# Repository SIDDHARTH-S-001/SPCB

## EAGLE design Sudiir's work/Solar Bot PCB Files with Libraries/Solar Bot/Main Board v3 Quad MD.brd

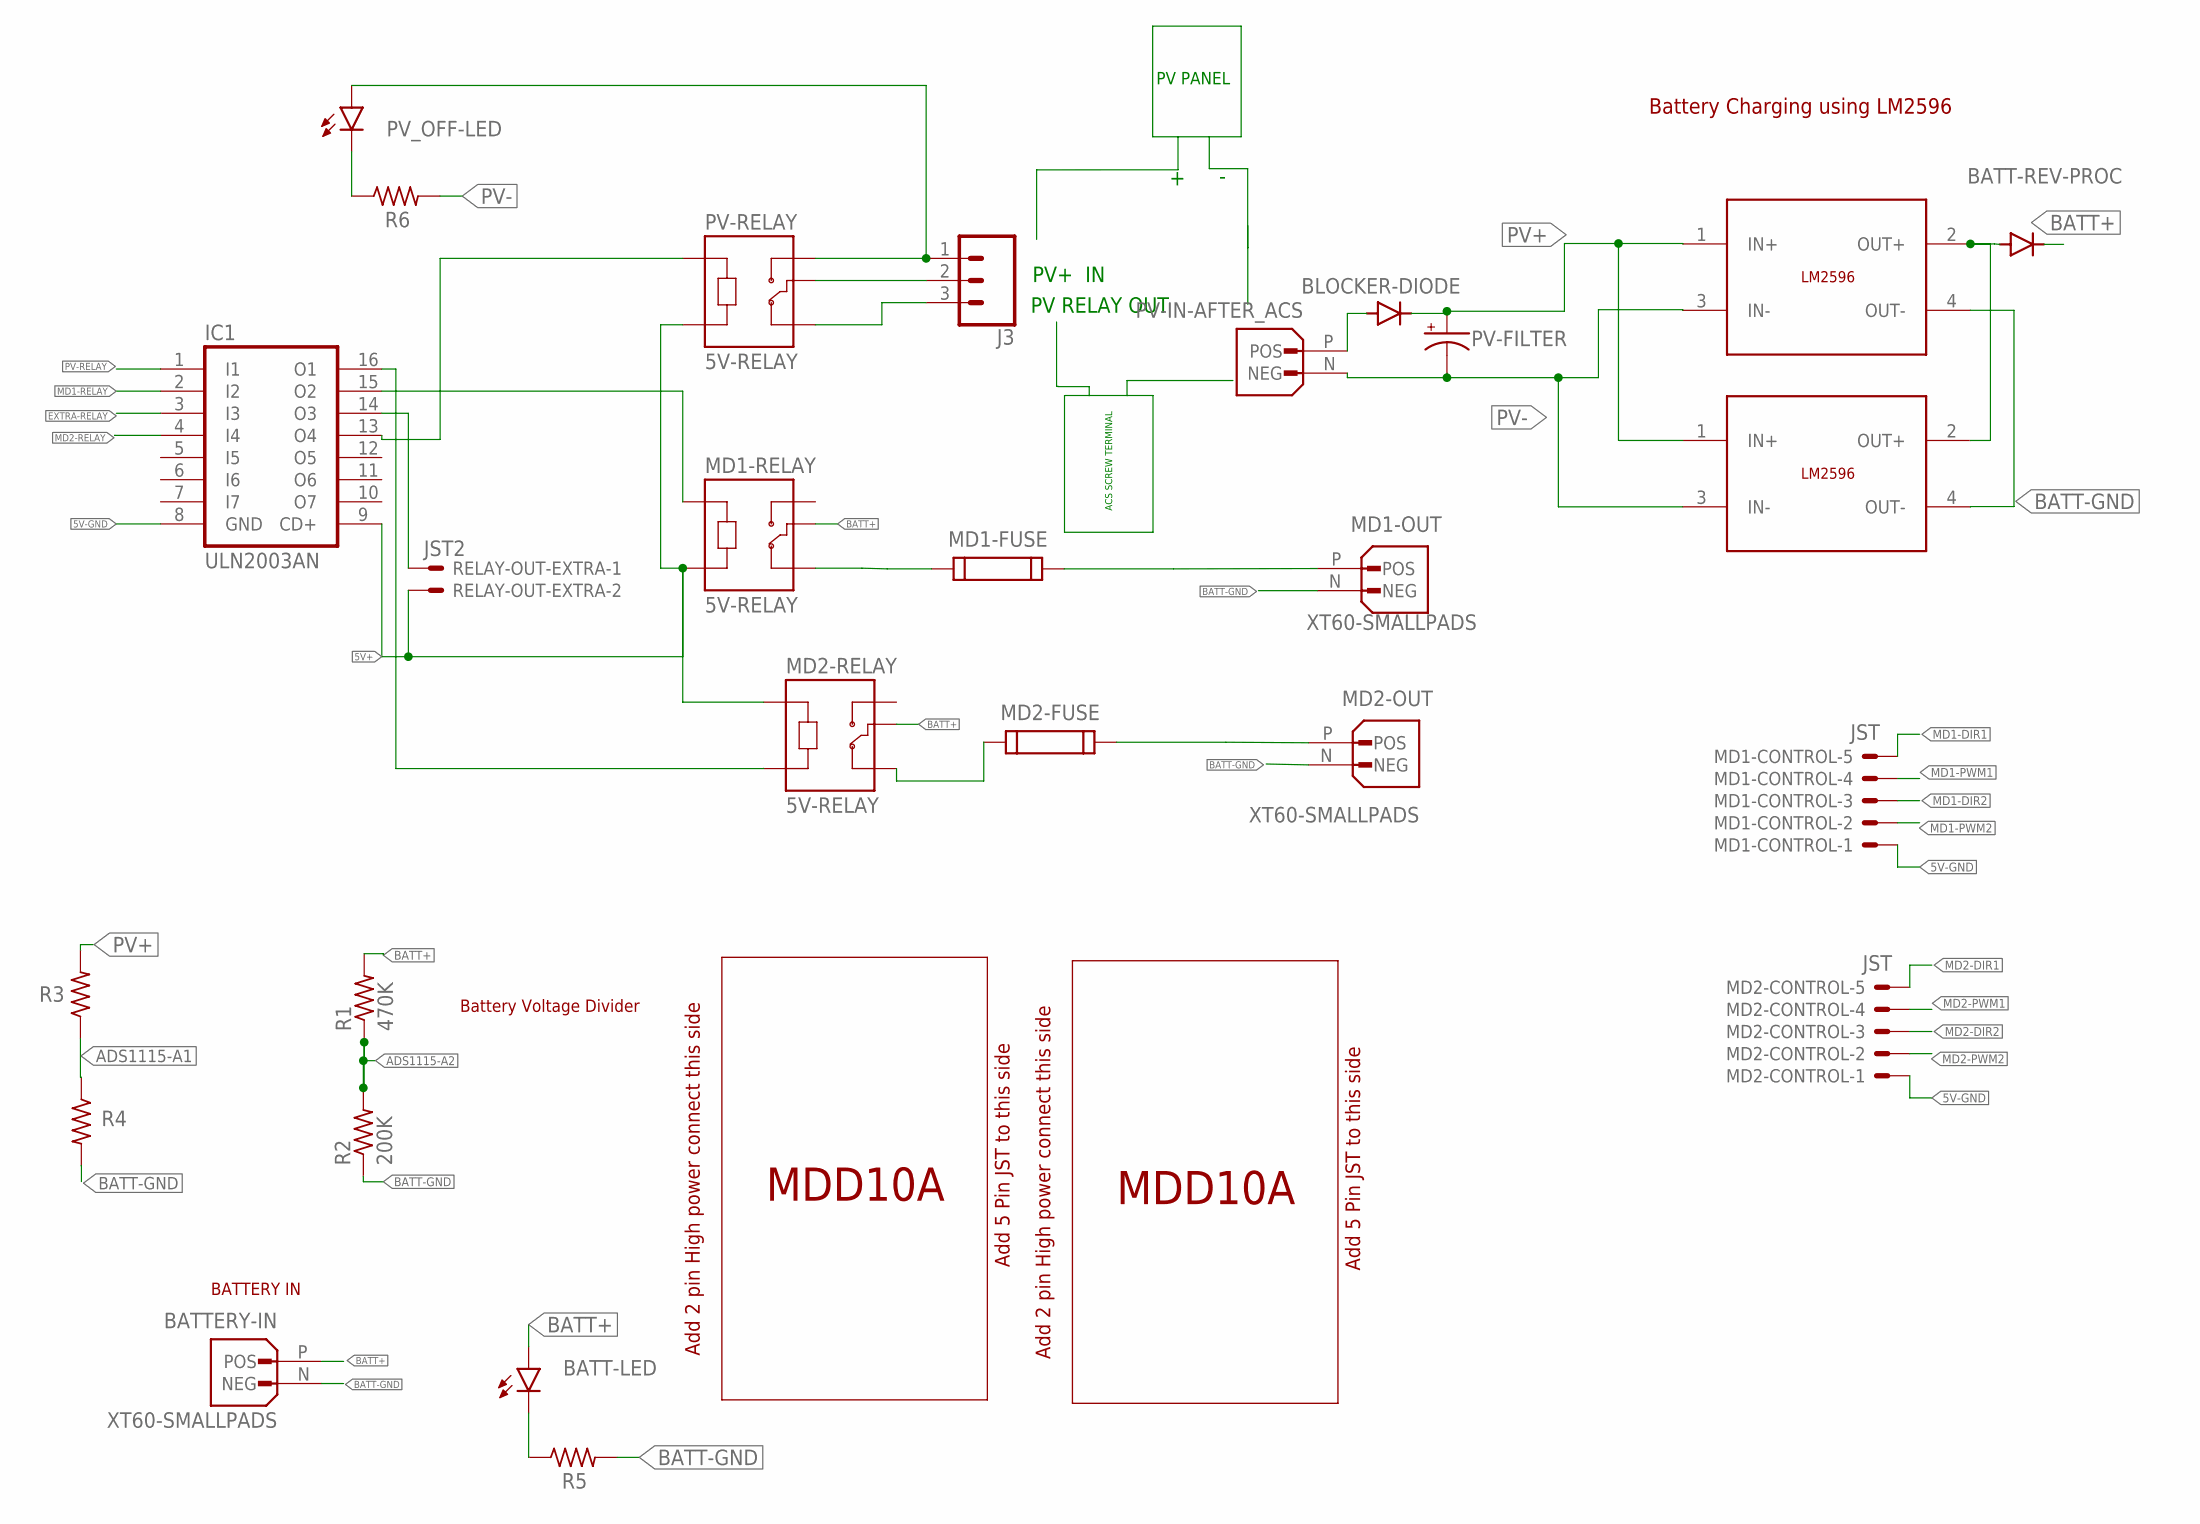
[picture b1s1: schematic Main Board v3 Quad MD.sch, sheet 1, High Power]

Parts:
BATT-LED: SFH482
BATT-REV-PROC: 1N5400; DO201-15
BATTERY-IN: XT60-SMALLPADS; XT-60-SMALLPADS
BLOCKER-DIODE: 1N5400; DO201-15
IC1: ULN2003AN; DIL16
J3: CONN_03SCREW_LOCK; SCREWTERMINAL-3.5MM-3_LOCK.007S
MD1-CONTROL, MD2-CONTROL: JST; JST-XH-05-PACKAGE-LONG-PAD
MD1-FUSE, MD2-FUSE: 696101000002
MD1-OUT, MD2-OUT: XT60-SMALLPADS; XT-60-SMALLPADS
MD1-RELAY, MD2-RELAY: 5V-RELAY; RELAY-SRD-05VDC-SL-C
PV-FILTER: CPOL-USE5-6; E5-6
PV-IN-AFTER_ACS: XT60-SMALLPADS; XT-60-SMALLPADS
PV-RELAY: 5V-RELAY; RELAY-SRD-05VDC-SL-C
PV_OFF-LED: SFH482
R1: 470K; 0309/12
R2: 200K; 0309/12
R3, R4, R5, R6: R-US_0309/12; 0309/12
RELAY-OUT-EXTRA: JST2; JST-XH-02-PACKAGE-LONG-PAD
U$1, U$2: LM2596-MODULE
U$3, U$7: MDD10A-MODULE; MDD10A

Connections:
5V+: IC1.9 (CD+), MD1-RELAY.A2, MD2-RELAY.A1, PV-RELAY.A2, RELAY-OUT-EXTRA.2; also elsewhere on the board
5V-GND: IC1.8 (GND), MD1-CONTROL.1, MD2-CONTROL.1; also elsewhere on the board
ADS1115-A1: R3.1, R4.1; also elsewhere on the board
ADS1115-A2: R1.1, R2.2; also elsewhere on the board
BATT+: BATT-LED.A, BATT-REV-PROC.C, BATTERY-IN.P (POS), MD1-RELAY.COM, MD2-RELAY.COM, R1.2; also elsewhere on the board
BATT-GND: BATTERY-IN.N (NEG), MD1-OUT.N (NEG), MD2-OUT.N (NEG), R2.1, R4.2, R5.2, U$1.4 (OUT-), U$2.4 (OUT-); also elsewhere on the board
EXTRA-RELAY: IC1.3 (I3); also elsewhere on the board
MD1-DIR1: MD1-CONTROL.5; also elsewhere on the board
MD1-DIR2: MD1-CONTROL.3; also elsewhere on the board
MD1-PWM1: MD1-CONTROL.4; also elsewhere on the board
MD1-PWM2: MD1-CONTROL.2; also elsewhere on the board
MD1-RELAY: IC1.2 (I2); also elsewhere on the board
MD2-DIR1: MD2-CONTROL.5; also elsewhere on the board
MD2-DIR2: MD2-CONTROL.3; also elsewhere on the board
MD2-PWM1: MD2-CONTROL.4; also elsewhere on the board
MD2-PWM2: MD2-CONTROL.2; also elsewhere on the board
MD2-RELAY: IC1.4 (I4); also elsewhere on the board
unnamed: MD1-FUSE.2, MD1-OUT.P (POS)
unnamed: IC1.14 (O3), RELAY-OUT-EXTRA.1
unnamed: J3.1, PV-RELAY.NO, PV_OFF-LED.A
unnamed: J3.2, PV-RELAY.COM
unnamed: MD1-FUSE.1, MD1-RELAY.NC
unnamed: MD2-FUSE.1, MD2-RELAY.NC
unnamed: BLOCKER-DIODE.A, PV-IN-AFTER_ACS.P (POS)
unnamed: IC1.16 (O1), MD2-RELAY.A2
unnamed: MD2-FUSE.2, MD2-OUT.P (POS)
unnamed: BATT-REV-PROC.A, U$1.2 (OUT+), U$2.2 (OUT+)
unnamed: IC1.13 (O4), PV-RELAY.A1
unnamed: BATT-LED.K (C), R5.1
unnamed: PV_OFF-LED.K (C), R6.1
unnamed: J3.3, PV-RELAY.NC
unnamed: IC1.15 (O2), MD1-RELAY.A1
PV+: BLOCKER-DIODE.C, PV-FILTER.+, R3.2, U$1.1 (IN+), U$2.1 (IN+)
PV-: PV-FILTER.-, PV-IN-AFTER_ACS.N (NEG), R6.2, U$1.3 (IN-), U$2.3 (IN-)
PV-RELAY: IC1.1 (I1); also elsewhere on the board

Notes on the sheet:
PV+ IN
PV RELAY OUT
ACS SCREW TERMINAL
PV PANEL
Battery Voltage Divider
BATTERY IN
Battery Charging using LM2596

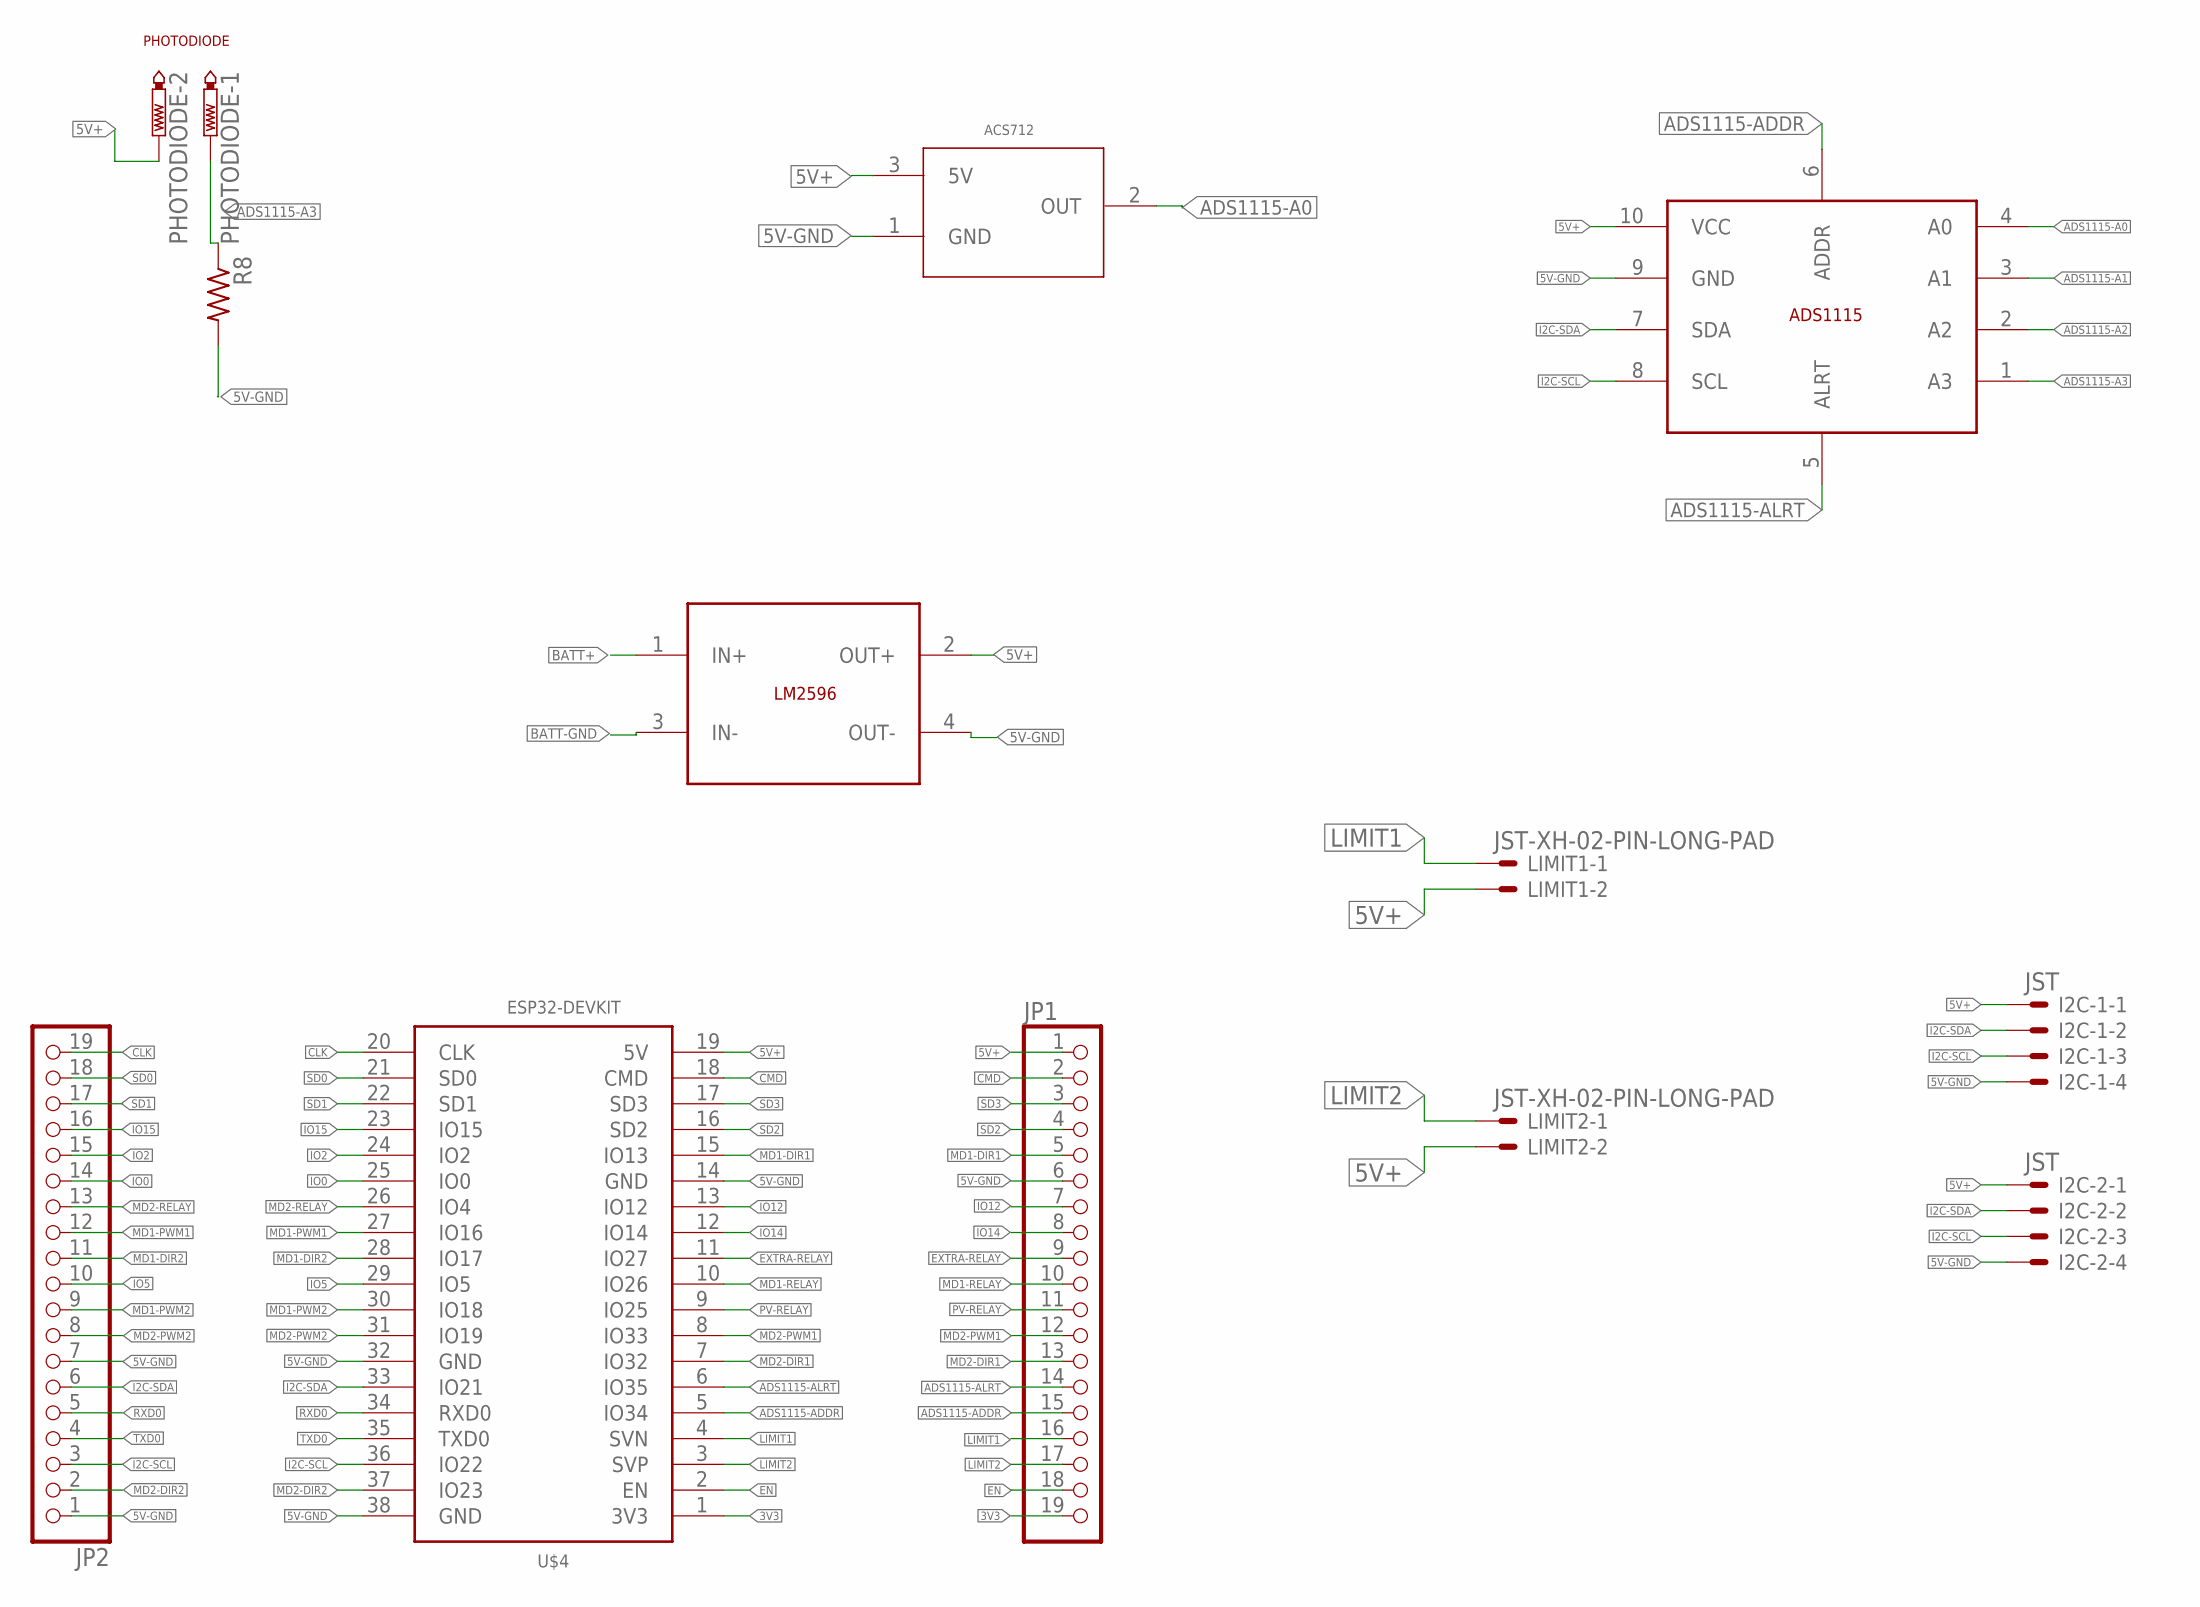
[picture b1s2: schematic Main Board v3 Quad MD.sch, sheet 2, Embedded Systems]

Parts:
I2C-1, I2C-2: JST; JST-XH-04-PACKAGE-LONG-PAD
JP1, JP2: PINHD-1X19; 1X19
LIMIT1, LIMIT2: JST-XH-02-PIN-LONG-PAD; JST-XH-02-PACKAGE-LONG-PAD
PHOTODIODE: PTR2; P2-38-17
R8: R-US_0309/12; 0309/12
U$4: ESP32-DEVKIT; ESP32-38PINS
U$5: ACS712-MODULE
U$6: ADS1115-MODULE
U$8: LM2596-MODULE

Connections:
3V3: JP1.19, U$4.1 (3V3)
5V+: I2C-1.1, I2C-2.1, JP1.1, LIMIT1.2, LIMIT2.2, PHOTODIODE.TP-2, U$4.19 (5V), U$5.3 (5V), U$6.10 (VCC), U$8.2 (OUT+); also elsewhere on the board
5V-GND: I2C-1.4, I2C-2.4, JP1.6, JP2.1, JP2.7, R8.2, U$4.14 (GND), U$4.32 (GND), U$4.38 (GND), U$5.1 (GND), U$6.9 (GND), U$8.4 (OUT-); also elsewhere on the board
ADS1115-A0: U$5.2 (OUT), U$6.4 (A0)
ADS1115-A1: U$6.3 (A1); also elsewhere on the board
ADS1115-A2: U$6.2 (A2); also elsewhere on the board
ADS1115-A3: PHOTODIODE.TP-1, R8.1, U$6.1 (A3)
ADS1115-ADDR: JP1.15, U$4.5 (IO34), U$6.6 (ADDR)
ADS1115-ALRT: JP1.14, U$4.6 (IO35), U$6.5 (ALRT)
BATT+: U$8.1 (IN+); also elsewhere on the board
BATT-GND: U$8.3 (IN-); also elsewhere on the board
CLK: JP2.19, U$4.20 (CLK)
CMD: JP1.2, U$4.18 (CMD)
EN: JP1.18, U$4.2 (EN)
EXTRA-RELAY: JP1.9, U$4.11 (IO27); also elsewhere on the board
I2C-SCL: I2C-1.3, I2C-2.3, JP2.3, U$4.36 (IO22), U$6.8 (SCL)
I2C-SDA: I2C-1.2, I2C-2.2, JP2.6, U$4.33 (IO21), U$6.7 (SDA)
IO0: JP2.14, U$4.25 (IO0)
IO2: JP2.15, U$4.24 (IO2)
IO5: JP2.10, U$4.29 (IO5)
IO12: JP1.7, U$4.13 (IO12)
IO14: JP1.8, U$4.12 (IO14)
IO15: JP2.16, U$4.23 (IO15)
LIMIT1: JP1.16, LIMIT1.1, U$4.4 (SVN)
LIMIT2: JP1.17, LIMIT2.1, U$4.3 (SVP)
MD1-DIR1: JP1.5, U$4.15 (IO13); also elsewhere on the board
MD1-DIR2: JP2.11, U$4.28 (IO17); also elsewhere on the board
MD1-PWM1: JP2.12, U$4.27 (IO16); also elsewhere on the board
MD1-PWM2: JP2.9, U$4.30 (IO18); also elsewhere on the board
MD1-RELAY: JP1.10, U$4.10 (IO26); also elsewhere on the board
MD2-DIR1: JP1.13, U$4.7 (IO32); also elsewhere on the board
MD2-DIR2: JP2.2, U$4.37 (IO23); also elsewhere on the board
MD2-PWM1: JP1.12, U$4.8 (IO33); also elsewhere on the board
MD2-PWM2: JP2.8, U$4.31 (IO19); also elsewhere on the board
MD2-RELAY: JP2.13, U$4.26 (IO4); also elsewhere on the board
PV-RELAY: JP1.11, U$4.9 (IO25); also elsewhere on the board
RXD0: JP2.5, U$4.34 (RXD0)
SD0: JP2.18, U$4.21 (SD0)
SD1: JP2.17, U$4.22 (SD1)
SD2: JP1.4, U$4.16 (SD2)
SD3: JP1.3, U$4.17 (SD3)
TXD0: JP2.4, U$4.35 (TXD0)

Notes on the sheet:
PHOTODIODE

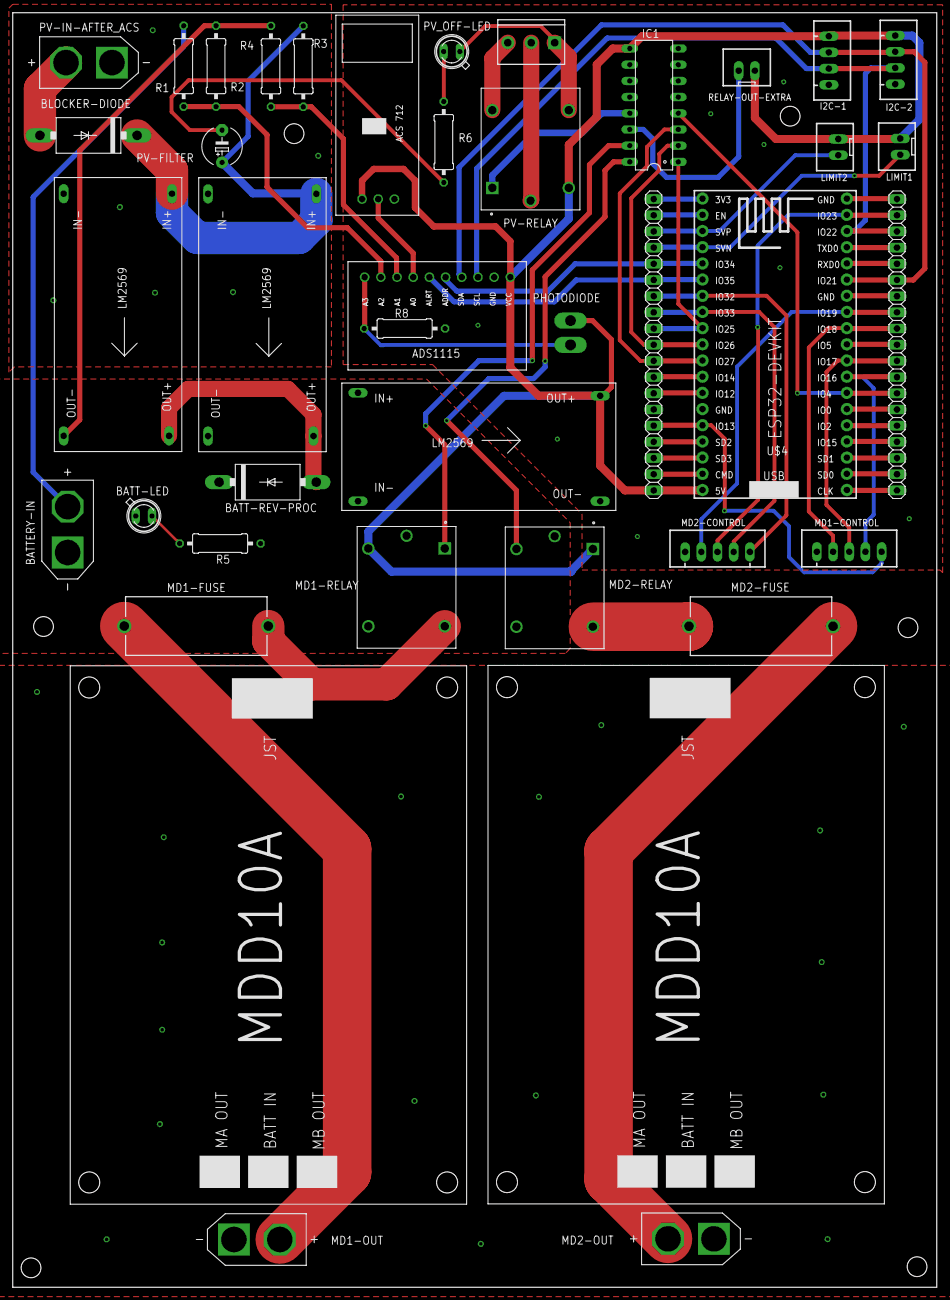
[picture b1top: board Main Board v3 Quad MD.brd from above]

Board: 2 copper layers, 145.0 x 200.0 mm, 41 parts (0 on the bottom side), 59 nets.

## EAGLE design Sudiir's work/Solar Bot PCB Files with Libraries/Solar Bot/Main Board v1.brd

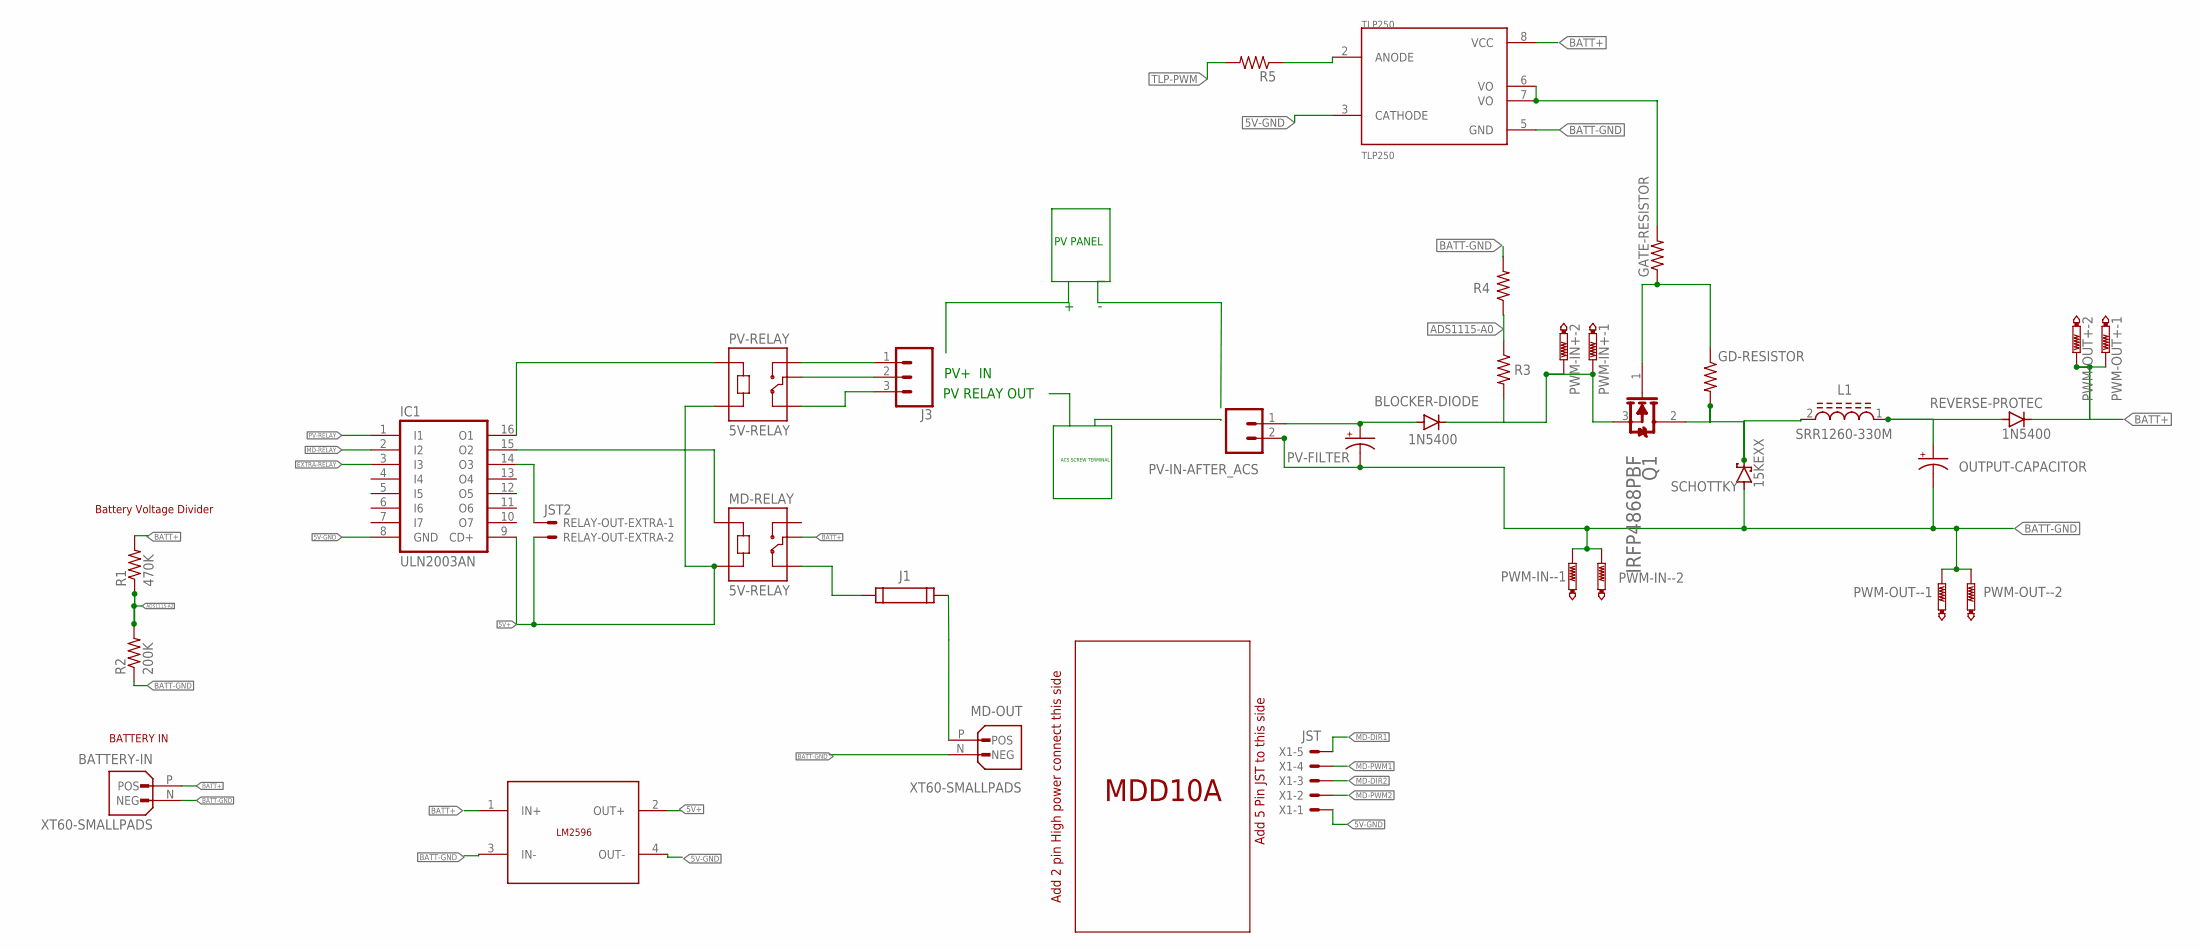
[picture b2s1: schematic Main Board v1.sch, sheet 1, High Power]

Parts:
BATTERY-IN: XT60-SMALLPADS; XT-60-SMALLPADS
BLOCKER-DIODE: 1N5400; DO201-15
GATE-RESISTOR: R-US_0309/12; 0309/12
GD-RESISTOR: R-US_0309/12; 0309/12
IC1: ULN2003AN; DIL16
J1: 696101000002
J3: CONN_03SCREW_LOCK; SCREWTERMINAL-3.5MM-3_LOCK.007S
L1: SRR1260-330M; INDP125125X600N
MD-OUT: XT60-SMALLPADS; XT-60-SMALLPADS
MD-RELAY: 5V-RELAY; RELAY-SRD-05VDC-SL-C
OUTPUT-CAPACITOR: 1000UF-RADIAL-5MM-25V-20%-NO-SILK; CPOL-RADIAL-5MM-10MM-NS
PV-FILTER: 1000UF-RADIAL-5MM-25V-20%-NO-SILK; CPOL-RADIAL-5MM-10MM-NS
PV-IN-AFTER_ACS: CONN_023.5MM; SCREWTERMINAL-3.5MM-2
PV-RELAY: 5V-RELAY; RELAY-SRD-05VDC-SL-C
PWM-IN+: PTR2; P2-38-17
PWM-IN-: PTR2; P2-38-17
PWM-OUT+: PTR2; P2-38-17
PWM-OUT-: PTR2; P2-38-17
Q1: INFINEON_IRFP4868PBFINFINEON_IRFP4868PBF_0_0; INFINEON_IRFP4868PBF_0
R1: 470K; 0309/12
R2: 200K; 0309/12
R3, R4, R5: R-US_0309/12; 0309/12
RELAY-OUT-EXTRA: JST2; JST-XH-02-PACKAGE-LONG-PAD
REVERSE-PROTEC: 1N5400; DO201-15
SCHOTTKY: 15KEXX; CB429-17
TLP250: TLP250; DIP8
U$2: MDD10A-MODULE; MDD10A
U$5: LM2596-MODULE
X1: JST; JST-XH-05-PACKAGE-LONG-PAD

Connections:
5V+: IC1.9 (CD+), MD-RELAY.A2, PV-RELAY.A2, RELAY-OUT-EXTRA.2, U$5.2 (OUT+); also elsewhere on the board
5V-GND: IC1.8 (GND), TLP250.3 (CATHODE), U$5.4 (OUT-), X1.1; also elsewhere on the board
ADS1115-A0: R3.1, R4.1; also elsewhere on the board
ADS1115-A2: R1.1, R2.2; also elsewhere on the board
BATT+: BATTERY-IN.P (POS), MD-RELAY.COM, PWM-OUT+.TP-1, PWM-OUT+.TP-2, R1.2, REVERSE-PROTEC.C, TLP250.8 (VCC), U$5.1 (IN+)
BATT-GND: BATTERY-IN.N (NEG), MD-OUT.N (NEG), OUTPUT-CAPACITOR.-, PV-FILTER.-, PV-IN-AFTER_ACS.2, PWM-IN-.TP-1, PWM-IN-.TP-2, PWM-OUT-.TP-1, PWM-OUT-.TP-2, R2.1, R4.2, SCHOTTKY.A, TLP250.5 (GND), U$5.3 (IN-)
EXTRA-RELAY: IC1.3 (I3); also elsewhere on the board
MD-DIR1: X1.5; also elsewhere on the board
MD-DIR2: X1.3; also elsewhere on the board
MD-PWM1: X1.4; also elsewhere on the board
MD-PWM2: X1.2; also elsewhere on the board
MD-RELAY: IC1.2 (I2); also elsewhere on the board
unnamed: J1.2, MD-OUT.P (POS)
unnamed: IC1.14 (O3), RELAY-OUT-EXTRA.1
unnamed: J3.1, PV-RELAY.NO
unnamed: J3.2, PV-RELAY.COM
unnamed: J1.1, MD-RELAY.NC
unnamed: L1.1, OUTPUT-CAPACITOR.+, REVERSE-PROTEC.A
unnamed: J3.3, PV-RELAY.NC
unnamed: IC1.16 (O1), PV-RELAY.A1
unnamed: IC1.15 (O2), MD-RELAY.A1
unnamed: GD-RESISTOR.2, L1.2, Q1.2 (D), SCHOTTKY.C
unnamed: R5.1, TLP250.2 (ANODE)
unnamed: BLOCKER-DIODE.A, PV-FILTER.+, PV-IN-AFTER_ACS.1
unnamed: GATE-RESISTOR.2, TLP250.6 (VO), TLP250.7 (VO)
unnamed: BLOCKER-DIODE.C, PWM-IN+.TP-1, PWM-IN+.TP-2, Q1.3 (S), R3.2
unnamed: GATE-RESISTOR.1, GD-RESISTOR.1, Q1.1 (G)
PV-RELAY: IC1.1 (I1); also elsewhere on the board
TLP-PWM: R5.2; also elsewhere on the board

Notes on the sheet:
PV+ IN
PV RELAY OUT
ACS SCREW TERMINAL
PV PANEL
Battery Voltage Divider
BATTERY IN

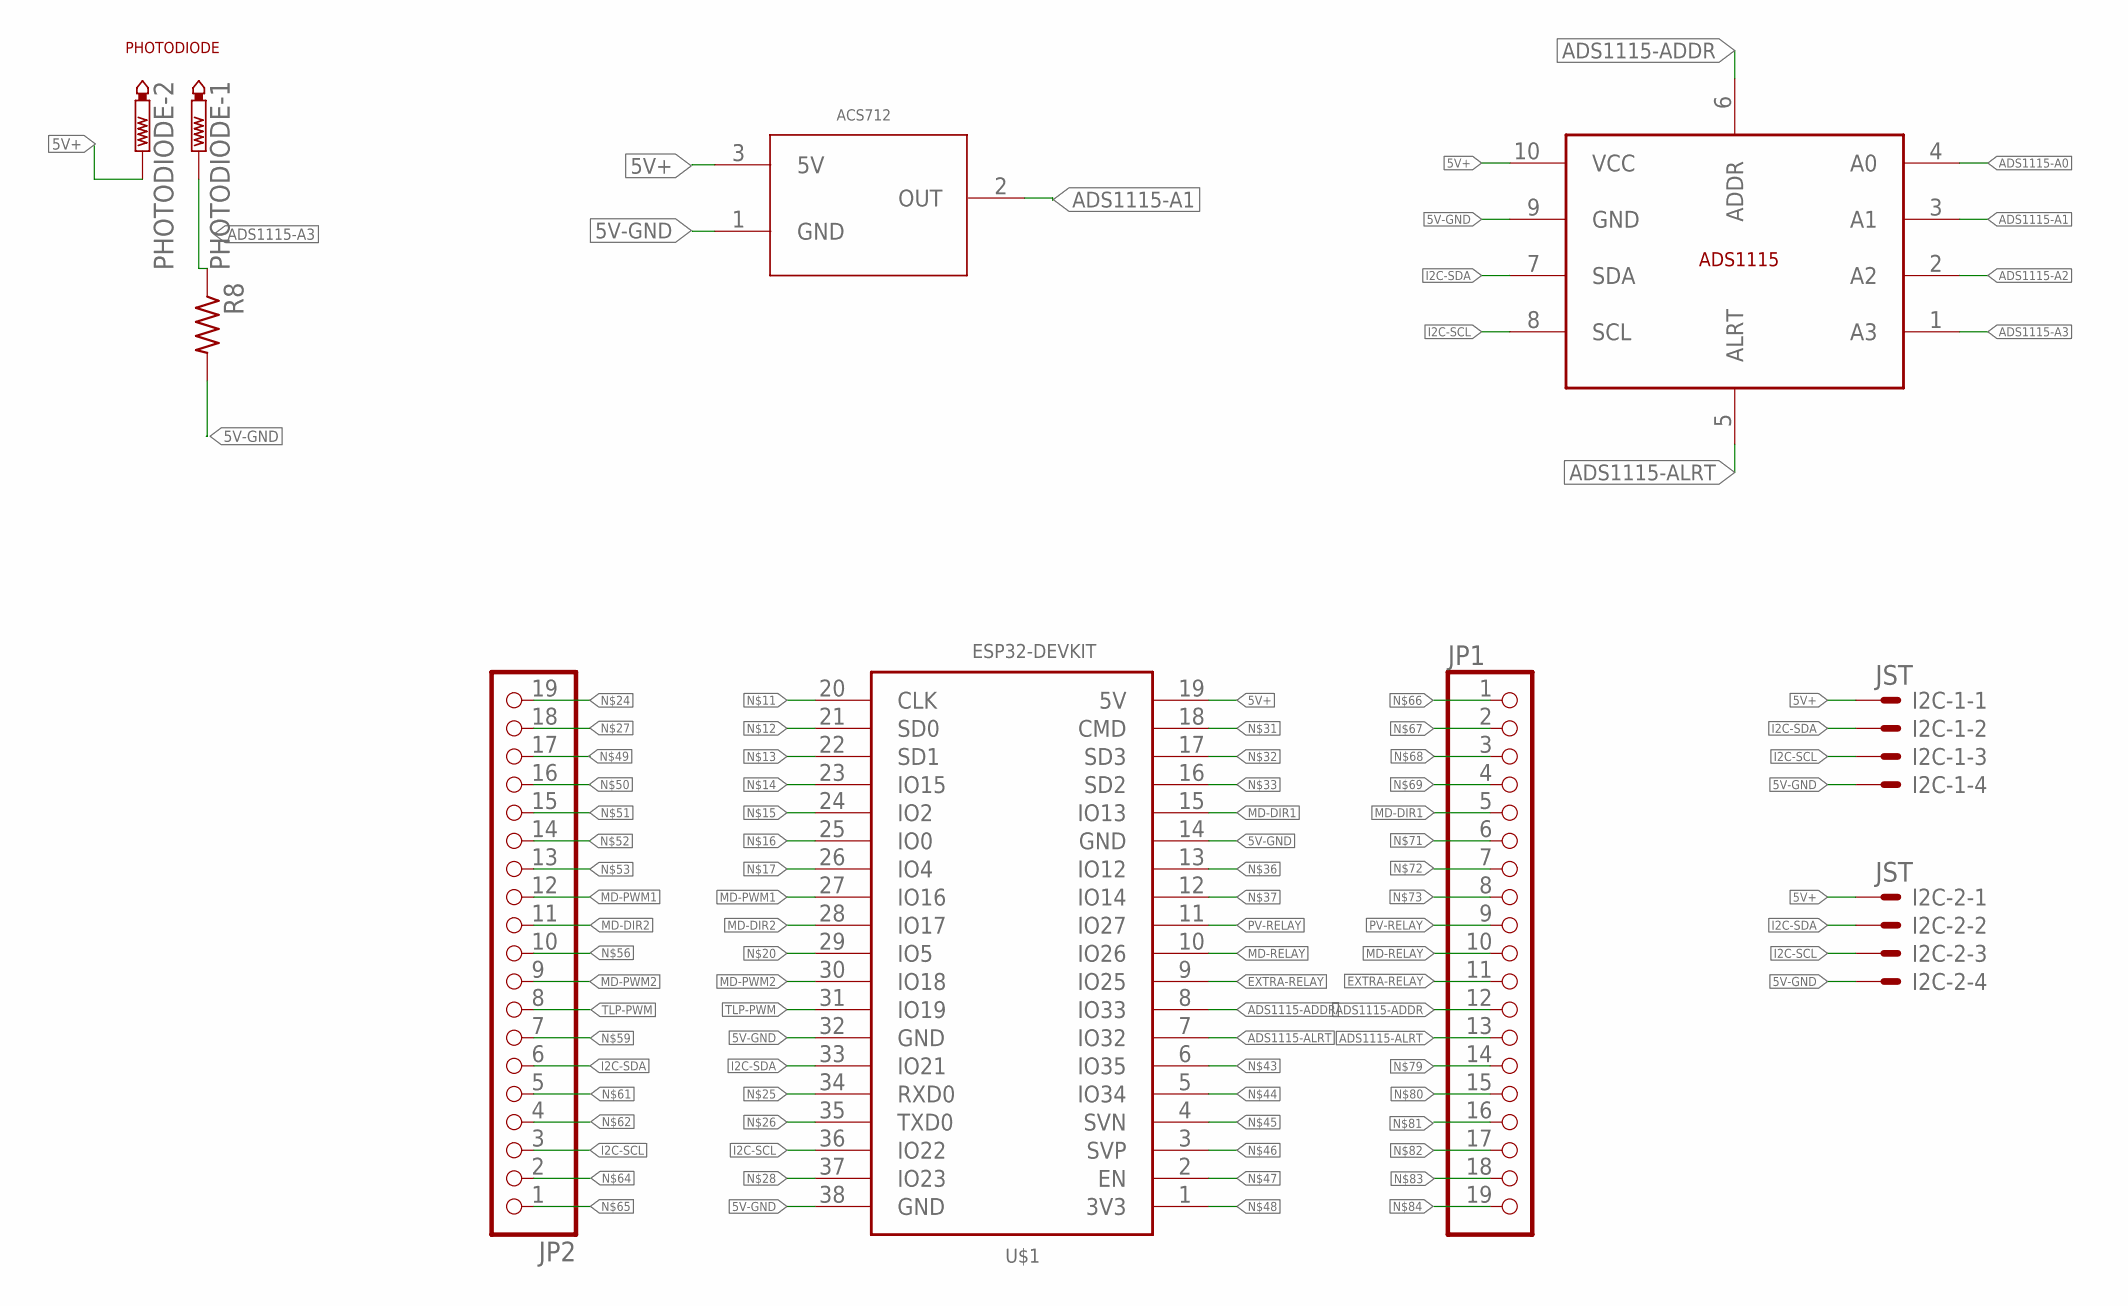
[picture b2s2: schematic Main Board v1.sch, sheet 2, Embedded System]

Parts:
I2C-1, I2C-2: JST; JST-XH-04-PACKAGE-LONG-PAD
JP1, JP2: PINHD-1X19; 1X19
PHOTODIODE: PTR2; P2-38-17
R8: R-US_0309/12; 0309/12
U$1: ESP32-DEVKIT; ESP32-38PINS
U$3: ACS712-MODULE
U$4: ADS1115-MODULE

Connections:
5V+: I2C-1.1, I2C-2.1, PHOTODIODE.TP-2, U$1.19 (5V), U$3.3 (5V), U$4.10 (VCC); also elsewhere on the board
5V-GND: I2C-1.4, I2C-2.4, R8.2, U$1.14 (GND), U$1.32 (GND), U$1.38 (GND), U$3.1 (GND), U$4.9 (GND); also elsewhere on the board
ADS1115-A0: U$4.4 (A0); also elsewhere on the board
ADS1115-A1: U$3.2 (OUT), U$4.3 (A1)
ADS1115-A2: U$4.2 (A2); also elsewhere on the board
ADS1115-A3: PHOTODIODE.TP-1, R8.1, U$4.1 (A3)
ADS1115-ADDR: JP1.12, U$1.8 (IO33), U$4.6 (ADDR)
ADS1115-ALRT: JP1.13, U$1.7 (IO32), U$4.5 (ALRT)
EXTRA-RELAY: JP1.11, U$1.9 (IO25); also elsewhere on the board
I2C-SCL: I2C-1.3, I2C-2.3, JP2.3, U$1.36 (IO22), U$4.8 (SCL)
I2C-SDA: I2C-1.2, I2C-2.2, JP2.6, U$1.33 (IO21), U$4.7 (SDA)
MD-DIR1: JP1.5, U$1.15 (IO13); also elsewhere on the board
MD-DIR2: JP2.11, U$1.28 (IO17); also elsewhere on the board
MD-PWM1: JP2.12, U$1.27 (IO16); also elsewhere on the board
MD-PWM2: JP2.9, U$1.30 (IO18); also elsewhere on the board
MD-RELAY: JP1.10, U$1.10 (IO26); also elsewhere on the board
PV-RELAY: JP1.9, U$1.11 (IO27); also elsewhere on the board
TLP-PWM: JP2.8, U$1.31 (IO19); also elsewhere on the board

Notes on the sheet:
PHOTODIODE

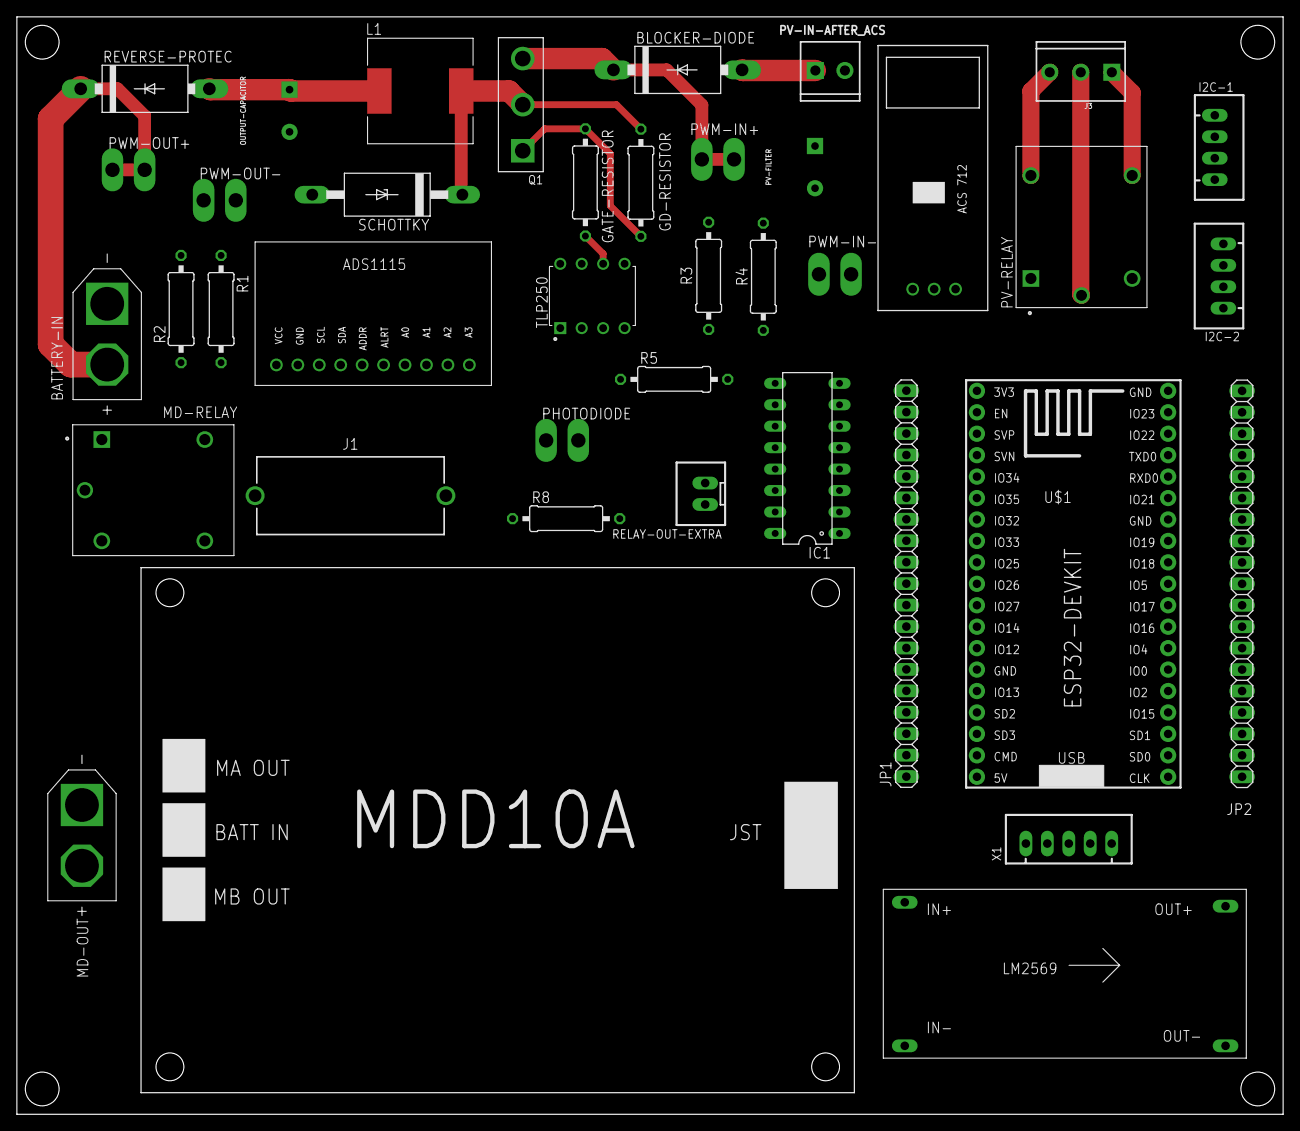
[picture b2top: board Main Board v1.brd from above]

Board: 2 copper layers, 150.0 x 130.0 mm, 40 parts (0 on the bottom side), 35 nets.

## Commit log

2023-04-11 Add files via upload
    Brush can now be operated in both directions at full speed.
2023-04-11 Add files via upload
    Brush can now be operated in both directions.
2023-04-11 Add files via upload
    Brush can be operated in both directions now.
2023-09-05 incorrect var fix
2023-10-27 output values maybe incorrect
2023-10-27 charging curve img
2023-10-27 add plotter
2023-11-04 lifepo4 curve data final
2023-11-04 sort out files

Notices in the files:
parts and their libraries:
Wurth_Connectors_WR-FSH: Copyright: Würth Elektronik
SparkFun-Connectors: Licensing: Creative Commons ShareAlike 4.0 International - https://creativecommons.org/licenses/by-sa/4.0
